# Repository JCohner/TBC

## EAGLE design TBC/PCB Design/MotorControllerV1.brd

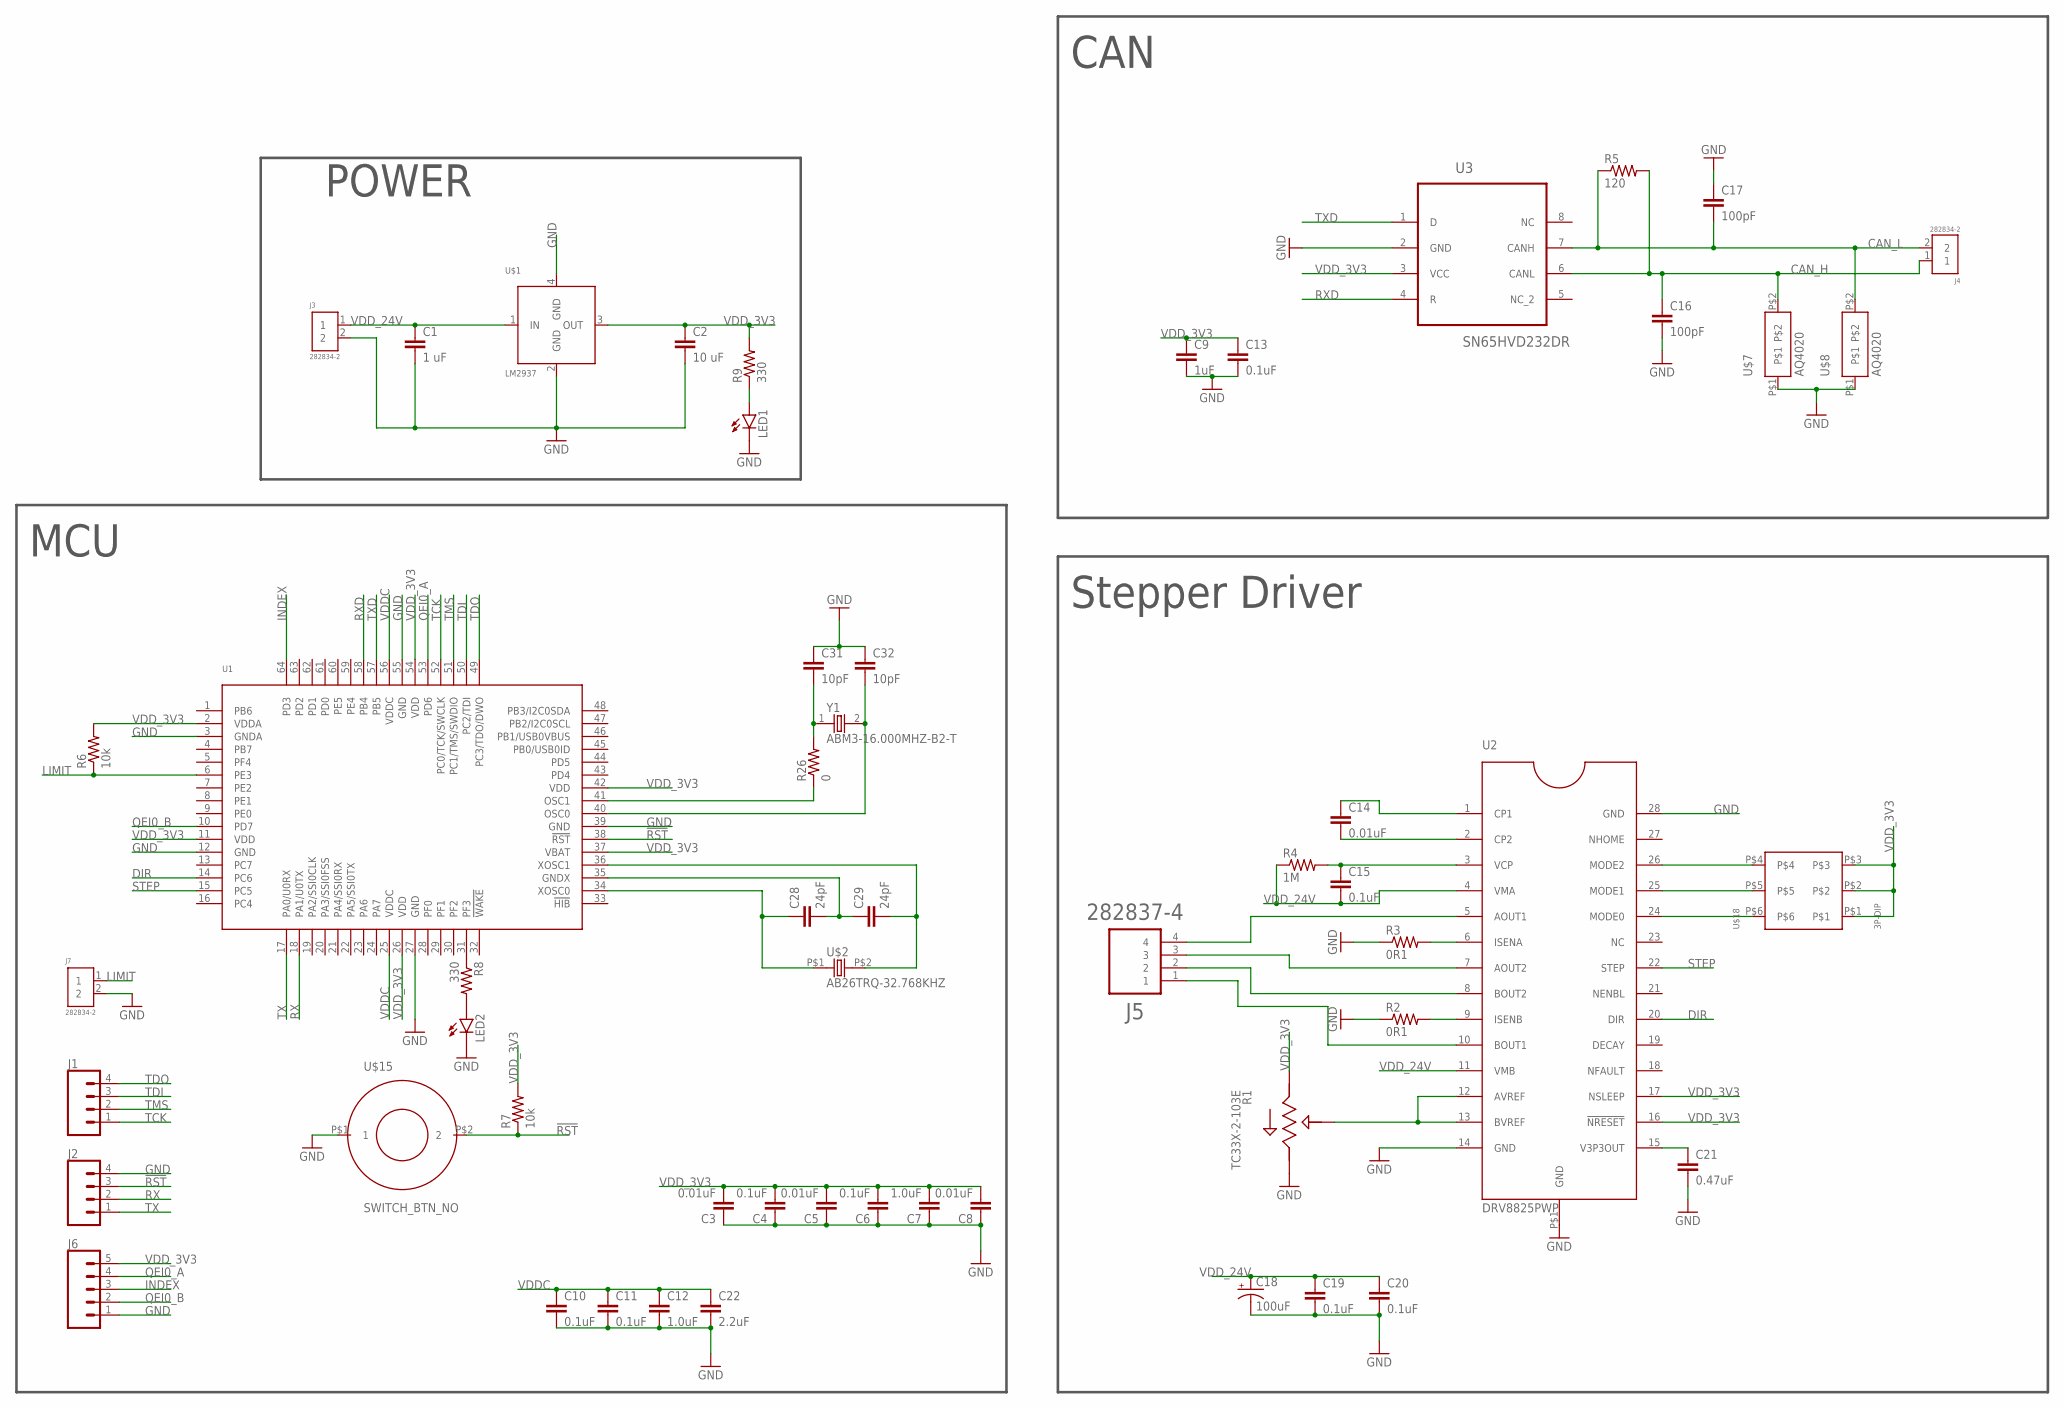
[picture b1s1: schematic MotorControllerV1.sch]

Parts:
C1: 1 uF; 0805
C2: 10 uF; 0805
C3, C5, C8, C14: 0.01uF; 0805
C4, C6, C10, C11, C13, C15: 0.1uF; 0805
C7, C12: 1.0uF; 0603
C9: 1uF; 0603
C16, C17: 100pF; 0603
C18: 100uF; CPOL-RADIAL-3.5MM-8MM
C19, C20: 0.1uF; 0603
C21: 0.47uF; 0603
C22: 2.2uF; 0805
C28, C29: 24pF; 0805
C31, C32: 10pF; 0805
J1, J2: CONN_04; 1X04
J3, J4, J7: 282834-2; CONN_282834-2
J5: 282837-4; TE_282837-4
J6: CONN_05; 1X05
LED1, LED2: LED0603; LED-0603
R1: TC33X-2-103E; 35WR
R2, R3: 0R1; 0805
R4: 1M; 0603
R5: 120; 0603
R6, R7: 10k; 0603
R8, R9: 330; 0603
R26: 0; 0603
U1: TM4C123GH6PMI; QFP50P1200X1200X160-64N
U2: DRV8825PWP; SOP65P640X120-28N
U3: SN65HVD232DR; SOIC127P600X175-8N
U$1: LM2937; R-PDSO-G4
U$2: AB26TRQ-32.768KHZ; AB26TRQ
U$7, U$8: AQ4020; SOD323
U$15: SWITCH_BTN_NO; BTN_2
U$18: 3P-DIP; CFS-0302MB
Y1: ABM3-16.000MHZ-B2-T; XTAL500X320X130N

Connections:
!RST: J2.3, R7.P$1 (1), U1.38 (!RST), U$15.P$2 (2)
CAN_H: C16.P$1 (1), J4.1, R5.P$2 (2), U3.6 (CANL), U$7.P$2
CAN_L: C17.P$2 (2), J4.2, R5.P$1 (1), U3.7 (CANH), U$8.P$2
DIR: U1.14 (PC6), U2.20 (DIR)
GND: C1.2, C2.2, C3.1, C4.1, C5.1, C6.1, C7.P$1 (1), C8.1, C9.P$2 (2), C10.2, C11.2, C12.P$2 (2), C13.2, C16.P$2 (2), C17.P$1 (1), C18.2 (-), C19.P$2 (2), C20.P$2 (2), C21.P$2 (2), C22.2, C31.1, C32.1, J2.4, J3.2, J6.1, J7.2, LED1.C, LED2.C, R1.3, R2.1, R3.1, U1.3 (GNDA), U1.12 (GND), U1.27 (GND), U1.39 (GND), U1.55 (GND), U2.14 (GND), U2.28 (GND), U2.P$1 (GND), U3.2 (GND), U$1.2 (GND), U$1.4 (GND), U$7.P$1, U$8.P$1, U$15.P$1 (1)
INDEX: J6.3, U1.64 (PD3)
LIMIT: J7.1, R6.P$1 (1), U1.6 (PE3)
unnamed: C29.2, U1.36 (XOSC1), U$2.P$2 (2)
unnamed: C28.1, U1.34 (XOSC0), U$2.P$1 (1)
unnamed: C28.2, C29.1, U1.35 (GNDX)
unnamed: R26.P$1 (1), U1.41 (OSC1)
unnamed: LED1.A, R9.P$1 (1)
unnamed: C31.2, R26.P$2 (2), Y1.1
unnamed: C32.2, U1.40 (OSC0), Y1.2
unnamed: C14.2, U2.2 (CP2)
unnamed: C14.1, U2.1 (CP1)
unnamed: C15.1, R4.P$2 (2), U2.3 (VCP)
unnamed: J5.4, U2.5 (AOUT1)
unnamed: R1.2, U2.12 (AVREF), U2.13 (BVREF)
unnamed: J5.3, U2.7 (AOUT2)
unnamed: J5.2, U2.8 (BOUT2)
unnamed: J5.1, U2.10 (BOUT1)
unnamed: R3.2, U2.6 (ISENA)
unnamed: R2.2, U2.9 (ISENB)
unnamed: R8.P$1 (1), U1.31 (PF3)
unnamed: LED2.A, R8.P$2 (2)
unnamed: C21.P$1 (1), U2.15 (V3P3OUT)
unnamed: U2.26 (MODE2), U$18.P$4
unnamed: U2.25 (MODE1), U$18.P$5
unnamed: U2.24 (MODE0), U$18.P$6
QEI0_A: J6.4, U1.53 (PD6)
QEI0_B: J6.2, U1.10 (PD7)
RX: J2.2, U1.18 (PA1/U0TX)
RXD: U1.58 (PB4), U3.4 (R)
STEP: U1.15 (PC5), U2.22 (STEP)
TCK: J1.1, U1.52 (PC0/TCK/SWCLK)
TDI: J1.3, U1.50 (PC2/TDI)
TDO: J1.4, U1.49 (PC3/TDO/DWO)
TMS: J1.2, U1.51 (PC1/TMS/SWDIO)
TX: J2.1, U1.17 (PA0/U0RX)
TXD: U1.57 (PB5), U3.1 (D)
VDDC: C10.1, C11.1, C12.P$1 (1), C22.1, U1.25 (VDDC), U1.56 (VDDC)
VDD_3V3: C2.1, C3.2, C4.2, C5.2, C6.2, C7.P$2 (2), C8.2, C9.P$1 (1), C13.1, J6.5, R1.1, R6.P$2 (2), R7.P$2 (2), R9.P$2 (2), U1.2 (VDDA), U1.11 (VDD), U1.26 (VDD), U1.37 (VBAT), U1.42 (VDD), U1.54 (VDD), U2.16 (!NRESET), U2.17 (NSLEEP), U3.3 (VCC), U$1.3 (OUT), U$18.P$1, U$18.P$2, U$18.P$3
VDD_24V: C1.1, C15.2, C18.1 (+), C19.P$1 (1), C20.P$1 (1), J3.1, R4.P$1 (1), U2.4 (VMA), U2.11 (VMB), U$1.1 (IN)

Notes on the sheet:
POWER
CAN
Stepper Driver
MCU

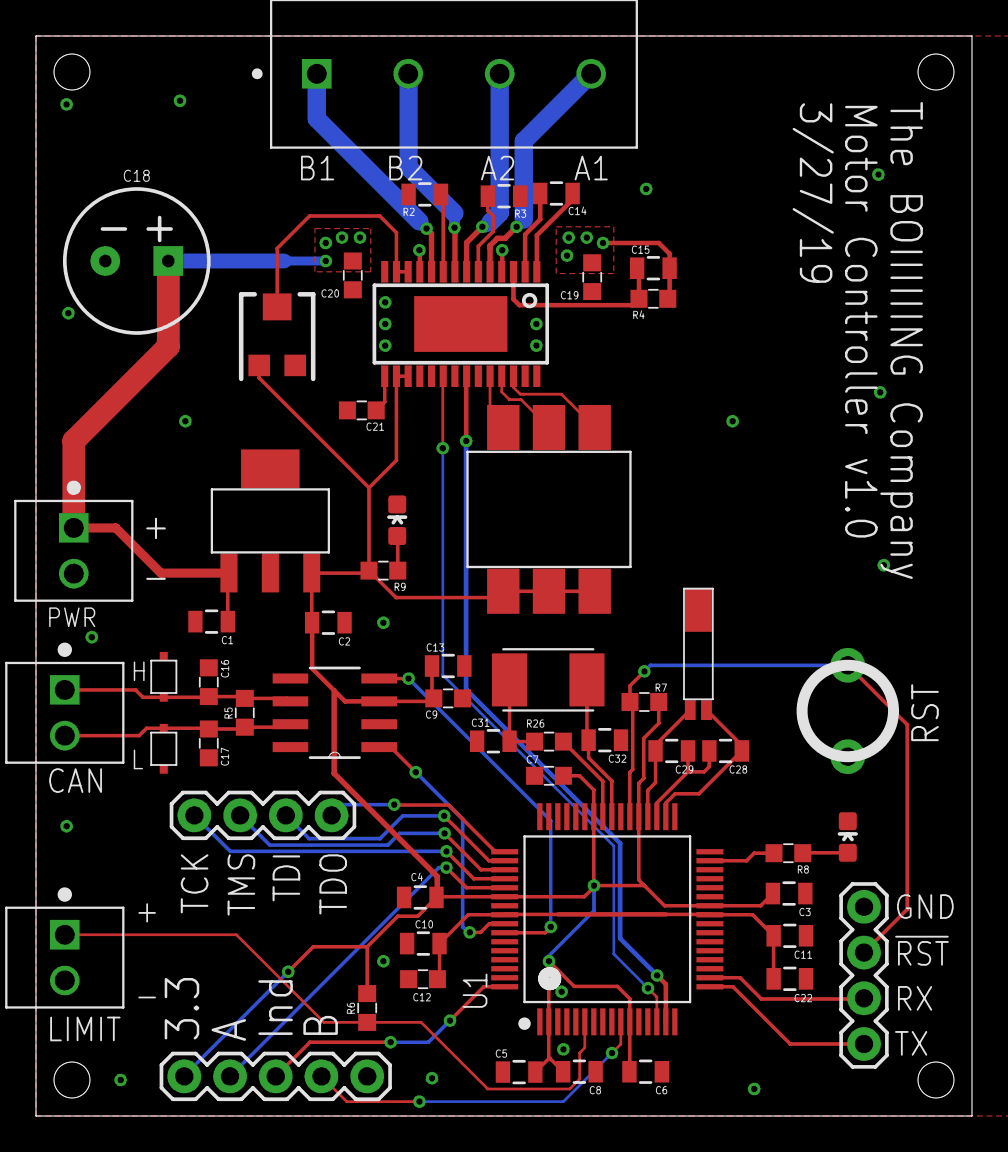
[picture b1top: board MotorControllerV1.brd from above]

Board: 2 copper layers, 52.0 x 60.0 mm, 55 parts (0 on the bottom side), 44 nets.

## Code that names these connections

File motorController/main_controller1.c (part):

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//! CANBUS implementation
//! - CAN0 peripheral
//! - GPIO port B peripheral (for CAN0 pins)
//! - CAN0RX - PB4
//! - CAN0TX - PB5
//! - INT_CAN0 - CANIntHandler
//*****************************************************************************
//! Console implementation
//! - UART0 peripheral
//! - GPIO port A peripheral (for UART0 pins)
//! - UART0RX - PA0
//! - UART0TX - PA1
//*****************************************************************************
//! Stepper implementation
//! - PWM3 peripheral
//! - GPIO port C peripheral (for PWM7 and DIR output)
//! - PWM7 - PC5
//! - DIR - PC6
//*****************************************************************************
//! QEI implementation
//! - QEI peripheral
//! - GPIO port D peripheral (for QEI0)
//! - Channel A - PD6
//! - Channel B - PD7
//! - Index - PD3
//*****************************************************************************

#define PERIOD 16000 // Period of PWM signal sent to stepper in clock ticks equal to 1 ms
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
void initStepper()
{
    // Setting up PWM on PC5
    SysCtlPeripheralEnable(SYSCTL_PERIPH_GPIOC);
    while(!SysCtlPeripheralReady(SYSCTL_PERIPH_GPIOC));

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    GPIOPinConfigure(GPIO_PD7_PHB0);
    GPIOPinConfigure(GPIO_PD3_IDX0);

    //Set GPIO pins for QEI. PhA0 -> PD6, PhB0 ->PD7. I believe this sets the pull up and makes them inputs
    GPIOPinTypeQEI(GPIO_PORTD_BASE, GPIO_PIN_3 | GPIO_PIN_6 |  GPIO_PIN_7);

    //DISable peripheral and int before configuration
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
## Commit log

2019-03-13 all bootstrap/html/js files for ui
2019-03-13 gou's code for ik
2019-03-13 init readme
2019-03-13 Initial Controller Firmware
    Main Controller with CAN and UART read enabled
    Motor Controller with CAN, Stepper Driver control, and QEI interface working
2019-03-14 latest html/bootstrap
2019-03-19 Changes made for Winter final presentation
    More CAN encoding to move stepper motor back and forth
2019-04-01 Motor Controller V1
    Schematic and board of motor controller v1 PCB
2019-04-02 successful pyserial com to ti
2019-04-04 initial connection from python script to matlab
2019-04-05 update merlet platform
2019-04-16 Main Controller PCB Designs
2019-04-18 mlapp with basic static implementation, can pass data to base workspace
2019-04-18 fleshing out dynamic test, adding buttons to begin testing
2019-04-24 matlabgui to python to tiva
2019-04-24 matlab UI
2019-04-24 with serial open and writes commented out
2019-04-25 more statefull serial data passing
2019-04-28 Updated Electrical BOM
2019-04-28 Code for controllers
2019-04-28 toggle button callback
2019-04-28 making serial com a little more robust
2019-04-29 lazy push work to pull from controllerfirmware
2019-04-30 Updated BOM
2019-05-01 working serial communication from matlab ui
2019-05-01 hello world example of matlab -> python connection
2019-05-01 hello world of python matlab engine connecting and accessing matlab
2019-05-01 pyserial hello world example
2019-05-01 Embedded serial communication
2019-05-10 control motors from matlab gui
2019-05-10 python conduit from matlab to tiva
2019-05-10 push newest version
2019-05-10 Updated Electical BOM
    Components for V2 of Main and Motor controller and V1 of Encoder
2019-05-12 with communication with tiva
2019-05-12 Modifying Filename to execute properly
    3.0 was not recognized as valid
2019-05-12 Adding Matlab to Tiva File
2019-05-12 Updating Kinematics to successful static motion
2019-05-13 Made the platform configuration more compact
2019-05-13 test
2019-05-14 kinematics for current platform
2019-05-14 dynamic test tiva code
2019-05-14 dynamic gui
2019-05-14 cleaned up and state machine-ifyed
2019-05-17 latest python com
2019-05-17 latest mlapp
2019-05-17 merlet ik
2019-05-17 w individual motor test
2019-05-17 working individual motor com
2019-05-17 wokring individual motor
2019-05-22 final packaging for software
2019-05-22 structure for static and dynamic loops implemented
2019-05-22 dynamic data capture implemented
2019-05-24 add dynamic matrix
2019-05-24 fixed guos communication edits so it works with new motor protocol
2019-05-24 fixed with serial write
2019-05-24 system working
2019-05-24 stashing
2019-05-24 matrix file
2019-05-28 test fk
2019-05-31 add communication_v2
2019-06-01 Updated BOM to final materials
2019-06-01 Updated firmware code
    Added helper functions and updated code structure to more of a state machine
2019-06-02 add waypoints test
2019-06-04 pyserial add waypoints test
2019-06-05 add maxium range
2019-06-06 logics refine
2019-06-07 dynamic
2019-06-07 add dynamic test
2019-06-07 new demo matrix
2019-06-12 Code Composer Projects
    Main controller and motor controller code
2019-06-12 bash scripts
2019-06-12 final communication.py

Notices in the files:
parts and their libraries:
SparkFun-Connectors: Licensing: Creative Commons ShareAlike 4.0 International - https://creativecommons.org/licenses/by-sa/4.0
